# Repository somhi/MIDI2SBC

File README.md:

# MIDI I2S SBC Pmod Edge Interface

STATUS (26/12/22): Finished gerber files for v1.10. See changelog for updates from v0.7 to v1.1

STATUS (24/03/22): Finished most of testing satisfactorily. 

STATUS (24/03/22): received pcbs (16/03/22) and started testing.  

STATUS (01/03/22): sent v0.70 to manufacturing at JLCPCB

### Intro

This board was born as an addon for [NeptUNO](https://github.com/neptuno-fpga/Main_nepUNO/wiki) FPGA platform (although it can be linked to other FPGAs) for interfacing with a MIDI synthesizer (mt32-pi), DAC I2S, single board computers (or microcontrollers) and pmod peripherals.

This is my first PCB design attempt. 

Project has been developed with KiCAD 6.0.

This design is based on the Eagle design of the RTC+I2S+PIzero Addon by [Antonio Villena](https://www.antoniovillena.es/store/). I have to thank Antonio for his help.

### Flow diagram

### **Schematic**

[addon-edge-rpi-i2s-pmod.pdf](addon-edge-rpi-i2s-pmod.pdf)

### **Features**

* MIDI synthesizer: [mt32-pi](https://github.com/dwhinham/mt32-pi) 
  
  * Play MIDI sounds from FPGA core through an I2S DAC
  * It is possible to send mt32-pi I2S audio back to FPGA for mixing with other core audio and play it back through the I2S DAC
  * PCB includes footprints for an I2C OLED display, a rotative encoder and 2 buttons
  * Control mt32-pi through i2c pins (e.g. from MiSTer's OSD)
  
* DAC I2S: 
  
  * Play I2S audio sent from your FPGA (connected to Edge or Pmod 4)
  * Play I2S audio from Raspberry mt32-pi
  * PCB includes footprints for UDA 1334A and PCM5102A
  
* SBC / Micro-controller interface (Multicore)
  * Interface to FPGAs through Edge or Pmod 4 connectors
  * Interface signals: SPI (6 signals) and UART (Rx/Tx) 
  * PCB includes footprint for Raspberry Pi model B 40 pin connector. Other SBCs or microcontrollers can be interfaced through adapters (e.g. MAix BiT and STM32 adapters are available in [Atlas FPGA project](https://github.com/atlasfpga))
  * A SBC or uC could be used as a multicore device for the FPGA
  
* UART header connected to FPGA (Rx, Tx) (and Raspberry Pi also)

**Additional features for the Edge connector ** 

* Compatible platforms: NeptUNO, ZXDOS+ and GomaDOS+ from [Antonio Villena](https://www.antoniovillena.es/store/). 
  * NeptUNO base board is compatible with most of QMTech FPGAs
* PMODs 1 & 2 for double Pmod peripherals (like Hyperram, VGA, HDMI, ....)
  * Pmod 1 is connected to I2C lines of NeptUNO base board
  * Includes a 5V power supply header between Pmods  for broader compatibility
* PMODs 3 & 4  
  * Can be used as host or peripheral pmods (jumper JP5 enables output power). 
  * Includes a 5V power supply pin between Pmods  for broader compatibility
  * Notes:
    * Double Pmod for peripherals is only possible if not using mt32-pi or multicore options
    * Pmod 3 cannot be used with NeptUNO board cores usign SRAM

### 3D model

### **Usage notes**

* It is recommended to power supply first the FPGA and thereafter the MISI2SBC addon
  
* DAC I2S 
  
  * Only one DAC (either UDA 1334A or PCM5102A) is intended to be used at the same time, although should be possible to run them simultaneously.
  * DAC input voltage can be selected by jumpers from Edge, Raspberry Pi or other FPGA
  * PCM5102A connector is compatible with a 6 pin Pmod if JP11 jumper is removed.
  
* SPI communication between Raspberry Pi and FPGA
  * SPI 0 or SPI 1 is available (selection by jumpers JP4x) 
  * External FPGAs are to be connected to Pmod4 (SPI + UART)

* mt32-pi synthesizer
  * Power supply: JP11 set to RPI and short JP12 with a jumper
  * DAC source from FPGA: SPI 1 should be selected when using mt32-pi (jumpers JP4x)
  * DAC source from RPi: No jumper or SPI 0 should be selected when using mt32-pi (jumpers JP4x)
  * External FPGAs are to be connected to Pmod I2S (PCM5102A) and MIDI In (UART) or Pmod4 (SPI + UART) for mixing.
  * MiSTer OSD i2c control: short jumpers JP31, JP32 and remove jumpers from JP41, JP45.

### **Jumpers / Switches selection**

The board has several jumpers for a broader usage with multiple configurations. Instead of right angle pin headers with jumpers is also possible to use 3 pin mini switches.

**Jumper types**

* 2 pin jumper is either shorted (jumper on) or disconnected (without jumper)

* 3 pin jumper is either on one side or the other always connecting the central pin

**Jumper selection**

* DAC I2S Power supply input source  

  * JP11:  RPI / EDGE   (3 pin jumper)
    * RPI (5V from Raspberry Pi)
    * EDGE (5V from Edge connector (NeptUNO FPGA))
  * JP12  (2 pin jumper)

    * Jumper shorting JP11 and VIN (5V from selection of JP11 jumper is applied to VIN)
    * Without jumper (DAC power input comes from any VIN pin (J4, J5 or J12 Vin itself))

* DAC I2S Audio Source (3 pin jumper)
  * DAC I2S connected to FPGA: I2S sound from MIDI synthesizer mt32-pi (MIDI_CLKBD, MIDI_WSBD, MIDI_DABD signals) is routed to the FPGA (where could be mixed with other core sounds) and the FPGA sends the I2S signals back to the DAC I2S (BCLK, WSEL, DIN signals).
    * JP21, JP22, JP23 jumper connected to the FPGA mark side
  * DAC I2S connected directly to the MIDI synthesizer (mt32-pi)
    * JP21, JP22, JP23   jumper connected to the RPI mark side

* SPI / I2C selection  (2 pin jumpers)

  * SPI selection: JP31 and JP32 open.
  * I2C selection: JP31 and JP32 closed (central pins of MOSI JP41 and CE1 JP45 are wired to the I2C bus connected to the mt32-pi (RPi). Jumpers JP41 and JP45 should be removed to avoid interferences).

* SPI selection: SPI0 or SPI1 (3 pin jumper)

  * SPI0: JP41, JP42, JP43, JP44, JP45  jumper connected to the SPI0 mark side
  * SPI1: JP41, JP42, JP43, JP44, JP45  jumper connected to the SPI1 mark side

* Power supply selection for pins 1 and 2 of the I2C OLED display

  * You might find in the marked I2C displays that need 3V3 on pin 1 and GND on pin 2 whereas others those pins are exchanged

  * JPS1 is a 3 pad solder jumper

    * Solder central pad to either 3V3 or GND for selecting function of PS1 display pin 1

  * JPS2 is a 3 pad solder jumper

    * Solder central pad to either 3V3 or GND for selecting function of PS2 display pin 2

* Power supply for PMOD3 & PMOD4 ( JP5 2 pin jumper )

  * Use as Peripheral pmods: JP5 opened  (No voltage is supplied into VH pins)
  * Use as Host pmods: JP5 closed (3V3 voltage from board is wired into VH pins)

### Notes regarding NeptUNO base board

* Following shared pins of Pmod 1 will only work with slow signals because they are connected to the I2C circuit of the VGA monitor. 

```
PMOD1_D2   I2C SCL    RTC,   VGA  
PMOD1_D3   I2C SDA    RTC,   VGA  
```

A simple way to solve this is to remove pins 12 and 15 with a plier from the VGA connector of the extension cable to the monitor as shown in the following picture:

* In order to use PMOD1_D5 pin it is required to configure in Quartus as following (Device and Pin Options : Dual-Purpose Pins: nCEO : Use as regular I/O)

* B24 Edge pin is connected in NeptUNO board internally to the Joy Select signal by means of a solder pad which by default is not soldered. To get this signal in the addon it is required to solder the two pads of the left as seen in the following picture.

  Please notice that it is better not to use the Joy Select pin if you intend the use also pin 7 on DB9 connectors of NeptUNO board for the joy select function of Sega megadrive joysticks.

### Changelog

v0.42  last version with 25 pins

v0.50  added 10 more pins connected at Edge connector to FPGA. Those pins are shared with other peripherals (2 pins bus I2C shared with RTC and VGA connector, 8 pins shared with SRAM memory)

v0.60  routed and gerber done

**v0.70** minor changes. Prototype version sent to manufacturing

v0.71 corrected minor misalignment between Pmod 1 and Pmod 2

v0.72 silkscreen updated (midi and mt32pi settings)

v1.00 silkscreen and documentation improved. Pmod3 and Pmod4 silkscreen labels exchanged. Rounded corners of outline. Pmod3/4 moved 0.4 mm outside.

v1.01 silkscreen for pmod i2s (PCM5102A connector). Improved usage notes in readme.

v1.02 minor silkscreen changes, usage notes.

v1.05 minor silkscreen changes

v1.10 routed i2c pins to PMOD 4 to communicate Raspberry Pi and FPGA (e.g. MiSTer can control mt32-pi from OSD)

### **Todo / Improvements**

* Mechanical stability of i2S DACs and display could be improved. -> Solution: bending a little bit the pins from the display and the DAC I2S so they fix better to the board sockets and don't move.

* Add in the same PCB a breokout board for converting PMO4 to USB3 for MiSTer connection

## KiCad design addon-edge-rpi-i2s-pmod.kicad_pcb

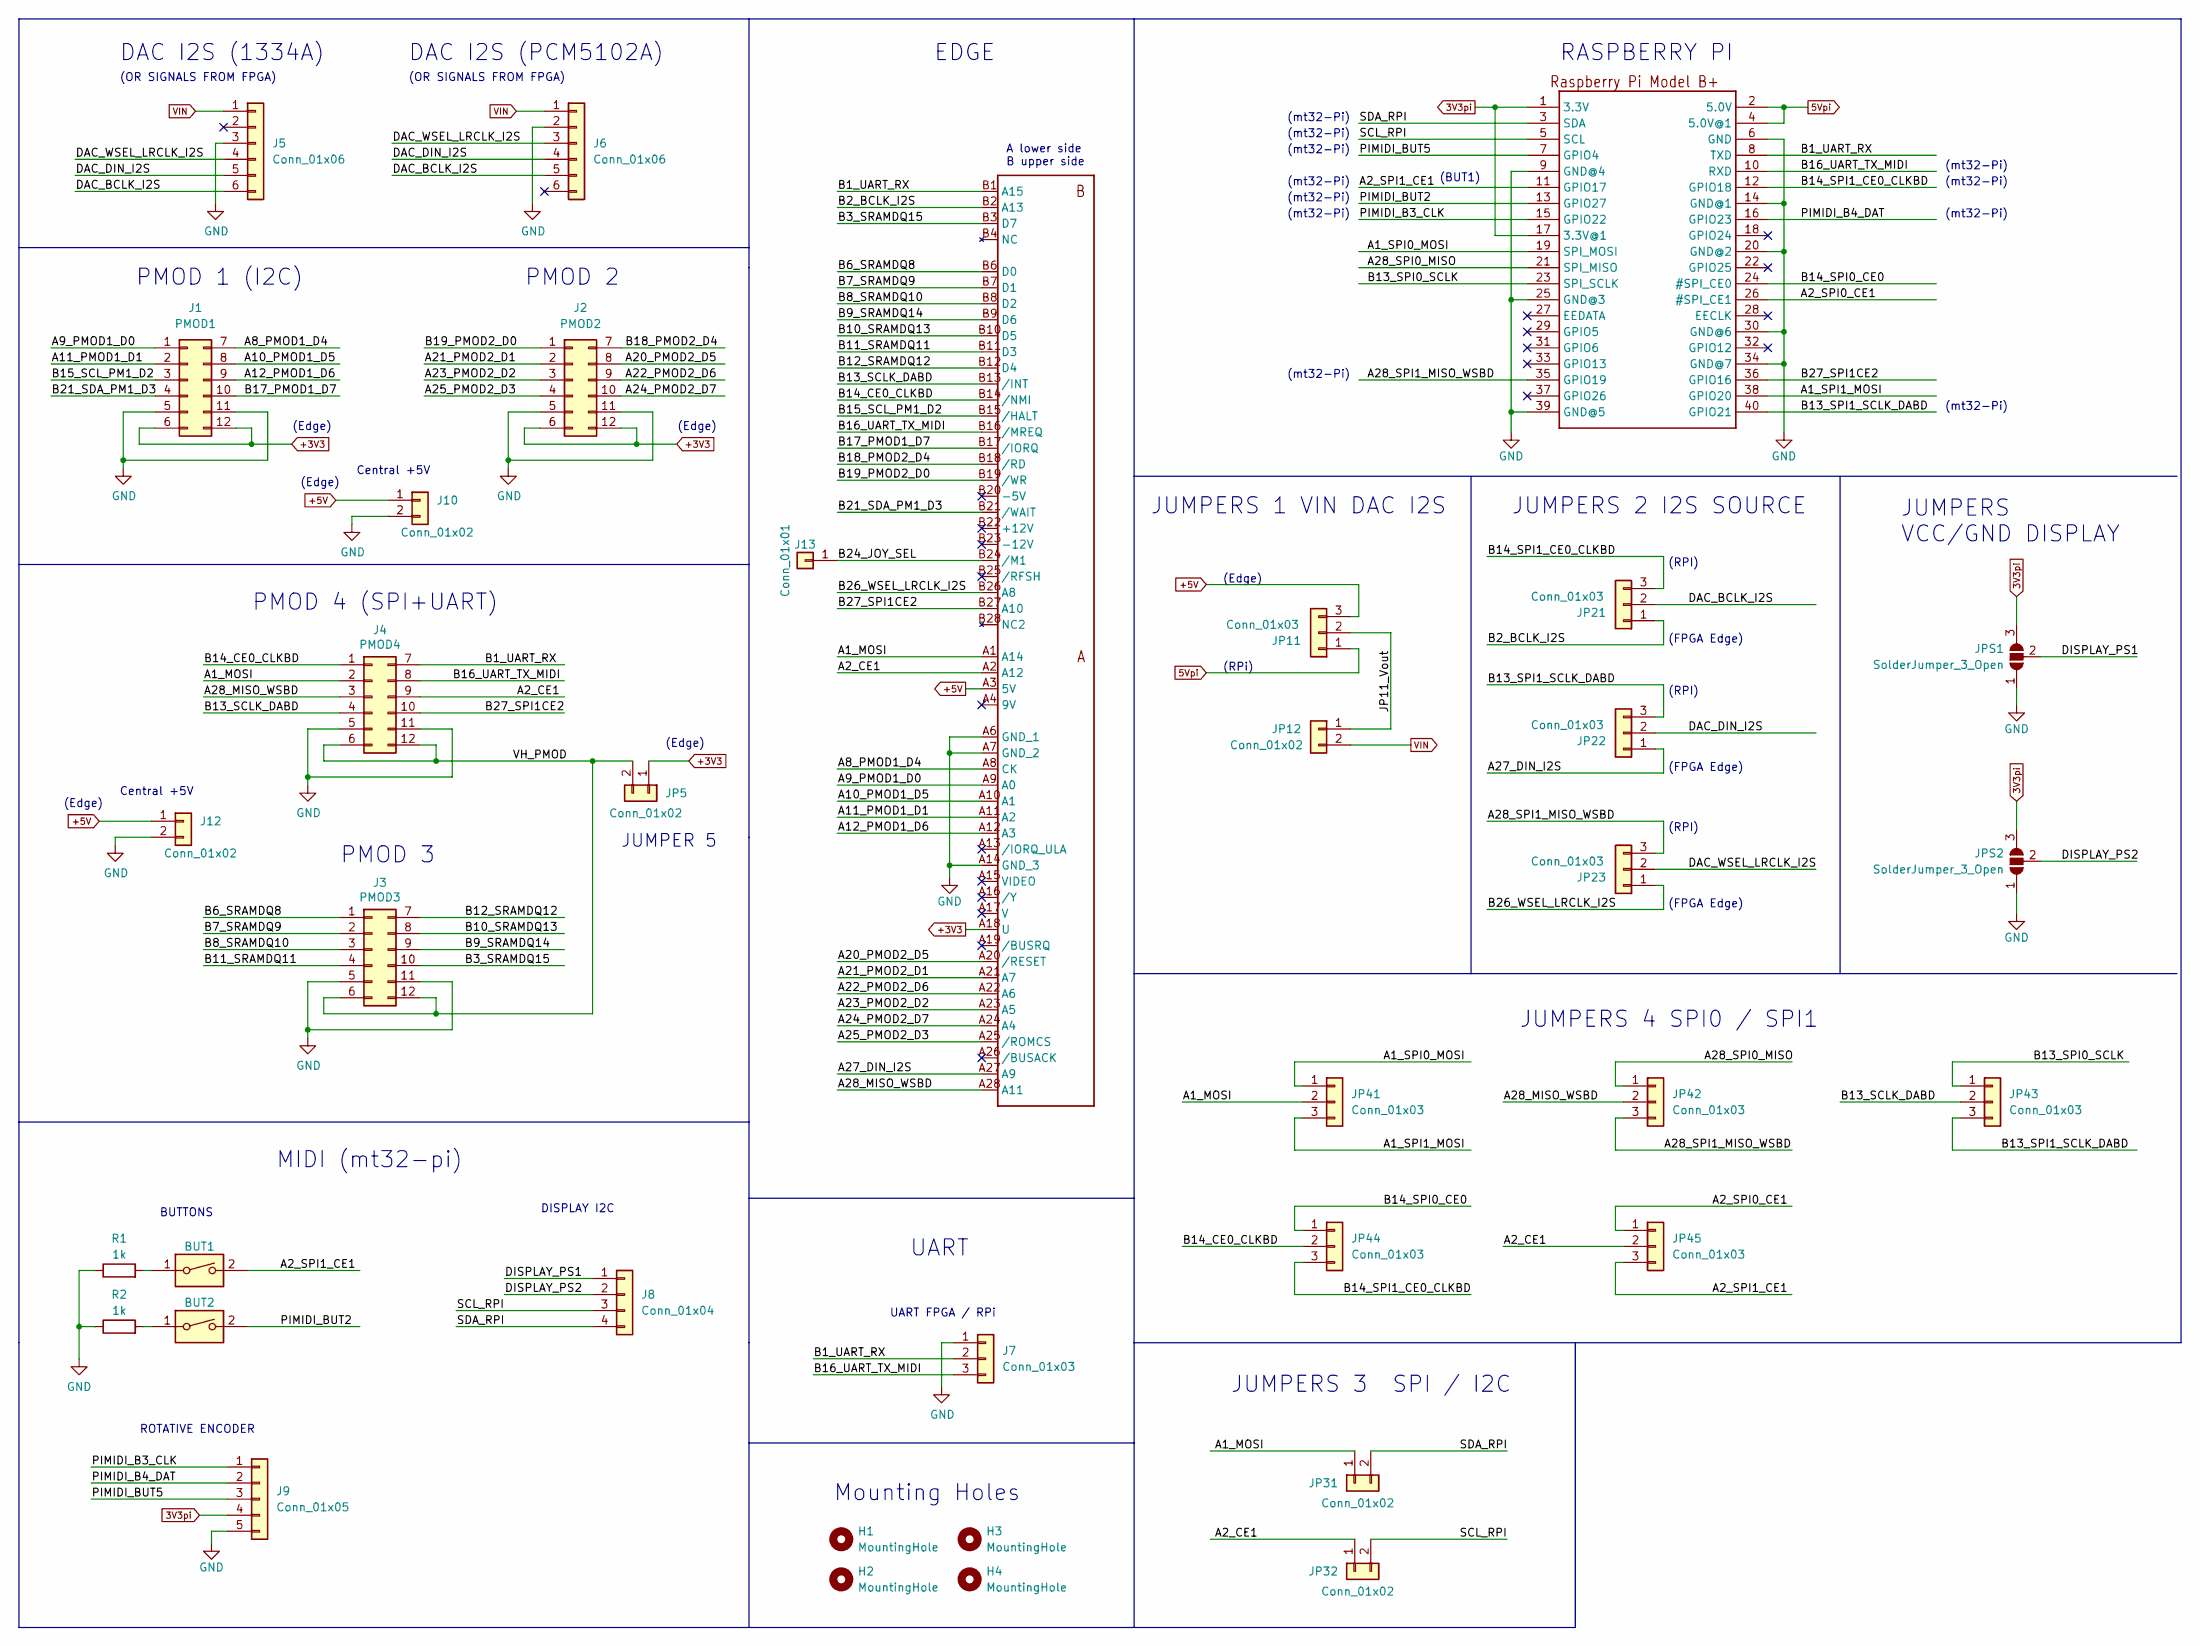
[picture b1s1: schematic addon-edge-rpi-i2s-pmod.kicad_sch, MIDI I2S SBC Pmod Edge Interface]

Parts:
BUT1, BUT2: SW_DIP_x01; SW_PUSH_6mm_H5mm
EDGE1: ZXSP_ED2X28_SPE_SOL_EDGE; 2X28_SPE2
H1, H2, H3, H4: MountingHole; MountingHole_3.2mm_M3
J1: PMOD1; Pmod_2x06_P2.54mm_Vertical_2
J2: PMOD2; Pmod_2x06_P2.54mm_Vertical_2
J3: PMOD3; PMOD_Female_Horizontal_2
J4: PMOD4; PMOD_Female_Horizontal_2
J5: Conn_01x06; UDA1334
J6: Conn_01x06; PCM5102
J7: Conn_01x03; PinHeader_1x03_P2.54mm_Vertical
J8: Conn_01x04; I2C_DISPLAY_MULTI2
J9: Conn_01x05; PinSocket_1x05_P2.54mm_Vertical
J10: Conn_01x02; PinSocket_1x02_P2.54mm_Vertical
J12: Conn_01x02; PinSocket_2x01_P2.54mm_Horizontal
J13: Conn_01x01; PinHeader_1x01_P2.54mm_Vertical
JP5, JP31, JP32: Conn_01x02; PinHeader_1x02_P2.54mm_Vertical
JP11, JP21, JP22, JP23, JP41, JP42, JP43, JP44, JP45: Conn_01x03; PinHeader_1x03_P2.54mm_Horizontal
JP12: Conn_01x02; PinHeader_1x02_P2.54mm_Horizontal
JPS1, JPS2: SolderJumper_3_Open; SolderJumper-3_P1.3mm_Open_RoundedPad1.0x1.5mm_NumberLabels
R1, R2: 1k; R_1206_3216Metric_Pad1.30x1.75mm_HandSolder
RPI1: RASPBERRYPI_BPLUS_BONNETNODIM; PinSocket_2x20_P2.54mm_Vertical

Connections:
3V3pi: J9.4, JPS1.3 (B), JPS2.3 (B), RPI1.1 (3.3V), RPI1.17 (3.3V@1)
5Vpi: JP11.1, RPI1.2 (5.0V), RPI1.4 (5.0V@1)
+3V3: EDGE1.A18 (U), J1.6, J1.12, J2.6, J2.12, JP5.1
+5V: EDGE1.A3 (5V), J10.1, J12.1, JP11.3
/A1_MOSI: EDGE1.A1 (A14), J4.2, JP31.1, JP41.2
/A1_SPI0_MOSI: JP41.1, RPI1.19 (SPI_MOSI)
/A1_SPI1_MOSI: JP41.3, RPI1.38 (GPIO20)
/A2_CE1: EDGE1.A2 (A12), J4.9, JP32.1, JP45.2
/A2_SPI0_CE1: JP45.1, RPI1.26 (#SPI_CE1)
/A2_SPI1_CE1: BUT1.2, JP45.3, RPI1.11 (GPIO17)
/A8_PMOD1_D4: EDGE1.A8 (CK), J1.7
/A9_PMOD1_D0: EDGE1.A9 (A0), J1.1
/A10_PMOD1_D5: EDGE1.A10 (A1), J1.8
/A11_PMOD1_D1: EDGE1.A11 (A2), J1.2
/A12_PMOD1_D6: EDGE1.A12 (A3), J1.9
/A20_PMOD2_D5: EDGE1.A20 (/RESET), J2.8
/A21_PMOD2_D1: EDGE1.A21 (A7), J2.2
/A22_PMOD2_D6: EDGE1.A22 (A6), J2.9
/A23_PMOD2_D2: EDGE1.A23 (A5), J2.3
/A24_PMOD2_D7: EDGE1.A24 (A4), J2.10
/A25_PMOD2_D3: EDGE1.A25 (/ROMCS), J2.4
/A27_DIN_I2S: EDGE1.A27 (A9), JP22.1
/A28_MISO_WSBD: EDGE1.A28 (A11), J4.3, JP42.2
/A28_SPI0_MISO: JP42.1, RPI1.21 (SPI_MISO)
/A28_SPI1_MISO_WSBD: JP23.3, JP42.3, RPI1.35 (GPIO19)
/B1_UART_RX: EDGE1.B1 (A15), J4.7, J7.2, RPI1.8 (TXD)
/B2_BCLK_I2S: EDGE1.B2 (A13), JP21.1
/B3_SRAMDQ15: EDGE1.B3 (D7), J3.10
/B6_SRAMDQ8: EDGE1.B6 (D0), J3.1
/B7_SRAMDQ9: EDGE1.B7 (D1), J3.2
/B8_SRAMDQ10: EDGE1.B8 (D2), J3.3
/B9_SRAMDQ14: EDGE1.B9 (D6), J3.9
/B10_SRAMDQ13: EDGE1.B10 (D5), J3.8
/B11_SRAMDQ11: EDGE1.B11 (D3), J3.4
/B12_SRAMDQ12: EDGE1.B12 (D4), J3.7
/B13_SCLK_DABD: EDGE1.B13 (/INT), J4.4, JP43.2
/B13_SPI0_SCLK: JP43.1, RPI1.23 (SPI_SCLK)
/B13_SPI1_SCLK_DABD: JP22.3, JP43.3, RPI1.40 (GPIO21)
/B14_CE0_CLKBD: EDGE1.B14 (/NMI), J4.1, JP44.2
/B14_SPI0_CE0: JP44.1, RPI1.24 (#SPI_CE0)
/B14_SPI1_CE0_CLKBD: JP21.3, JP44.3, RPI1.12 (GPIO18)
/B15_SCL_PM1_D2: EDGE1.B15 (/HALT), J1.3
/B16_UART_TX_MIDI: EDGE1.B16 (/MREQ), J4.8, J7.3, RPI1.10 (RXD)
/B17_PMOD1_D7: EDGE1.B17 (/IORQ), J1.10
/B18_PMOD2_D4: EDGE1.B18 (/RD), J2.7
/B19_PMOD2_D0: EDGE1.B19 (/WR), J2.1
/B21_SDA_PM1_D3: EDGE1.B21 (/WAIT), J1.4
/B24_JOY_SEL: EDGE1.B24 (/M1), J13.1
/B26_WSEL_LRCLK_I2S: EDGE1.B26 (A8), JP23.1
/B27_SPI1CE2: EDGE1.B27 (A10), J4.10, RPI1.36 (GPIO16)
/DAC_BCLK_I2S: J5.6, J6.5, JP21.2
/DAC_DIN_I2S: J5.5, J6.4, JP22.2
/DAC_WSEL_LRCLK_I2S: J5.4, J6.3, JP23.2
/DISPLAY_PS1: J8.1, JPS1.2 (C)
/DISPLAY_PS2: J8.2, JPS2.2 (C)
/JP11_Vout: JP11.2, JP12.1
/PIMIDI_B3_CLK: J9.1, RPI1.15 (GPIO22)
/PIMIDI_B4_DAT: J9.2, RPI1.16 (GPIO23)
/PIMIDI_BUT2: BUT2.2, RPI1.13 (GPIO27)
/PIMIDI_BUT5: J9.3, RPI1.7 (GPIO4)
/SCL_RPI: J8.3, JP32.2, RPI1.5 (SCL)
/SDA_RPI: J8.4, JP31.2, RPI1.3 (SDA)
/VH_PMOD: J3.6, J3.12, J4.6, J4.12, JP5.2
GND: EDGE1.A6 (GND_1), EDGE1.A7 (GND_2), EDGE1.A14 (GND_3), J1.5, J1.11, J2.5, J2.11, J3.5, J3.11, J4.5, J4.11, J5.3, J6.2, J7.1, J9.5, J10.2, J12.2, JPS1.1 (A), JPS2.1 (A), R1.1, R2.1, RPI1.6 (GND), RPI1.9 (GND@4), RPI1.14 (GND@1), RPI1.20 (GND@2), RPI1.25 (GND@3), RPI1.30 (GND@6), RPI1.34 (GND@7), RPI1.39 (GND@5)
unnamed: BUT1.1, R1.2
unnamed: BUT2.1, R2.2
VIN: J5.1, J6.1, JP12.2

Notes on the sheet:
JUMPERS 1 VIN DAC I2S
(mt32-Pi)
JUMPERS VCC/GND DISPLAY
PMOD 3
Central +5V
JUMPERS 4 SPI0 / SPI1
(RPI)
JUMPERS 2 I2S SOURCE
(OR SIGNALS FROM FPGA)
PMOD 4 (SPI+UART)
PMOD 1 (I2C)
Mounting Holes
UART FPGA / RPi
DISPLAY I2C
EDGE
(FPGA Edge)
(Edge)
(BUT1)
RASPBERRY PI
JUMPERS 3 SPI / I2C
UART
MIDI (mt32-pi)
JUMPER 5
ROTATIVE ENCODER
BUTTONS
(RPi)
PMOD 2
DAC I2S (1334A)
A lower side B upper side
DAC I2S (PCM5102A)

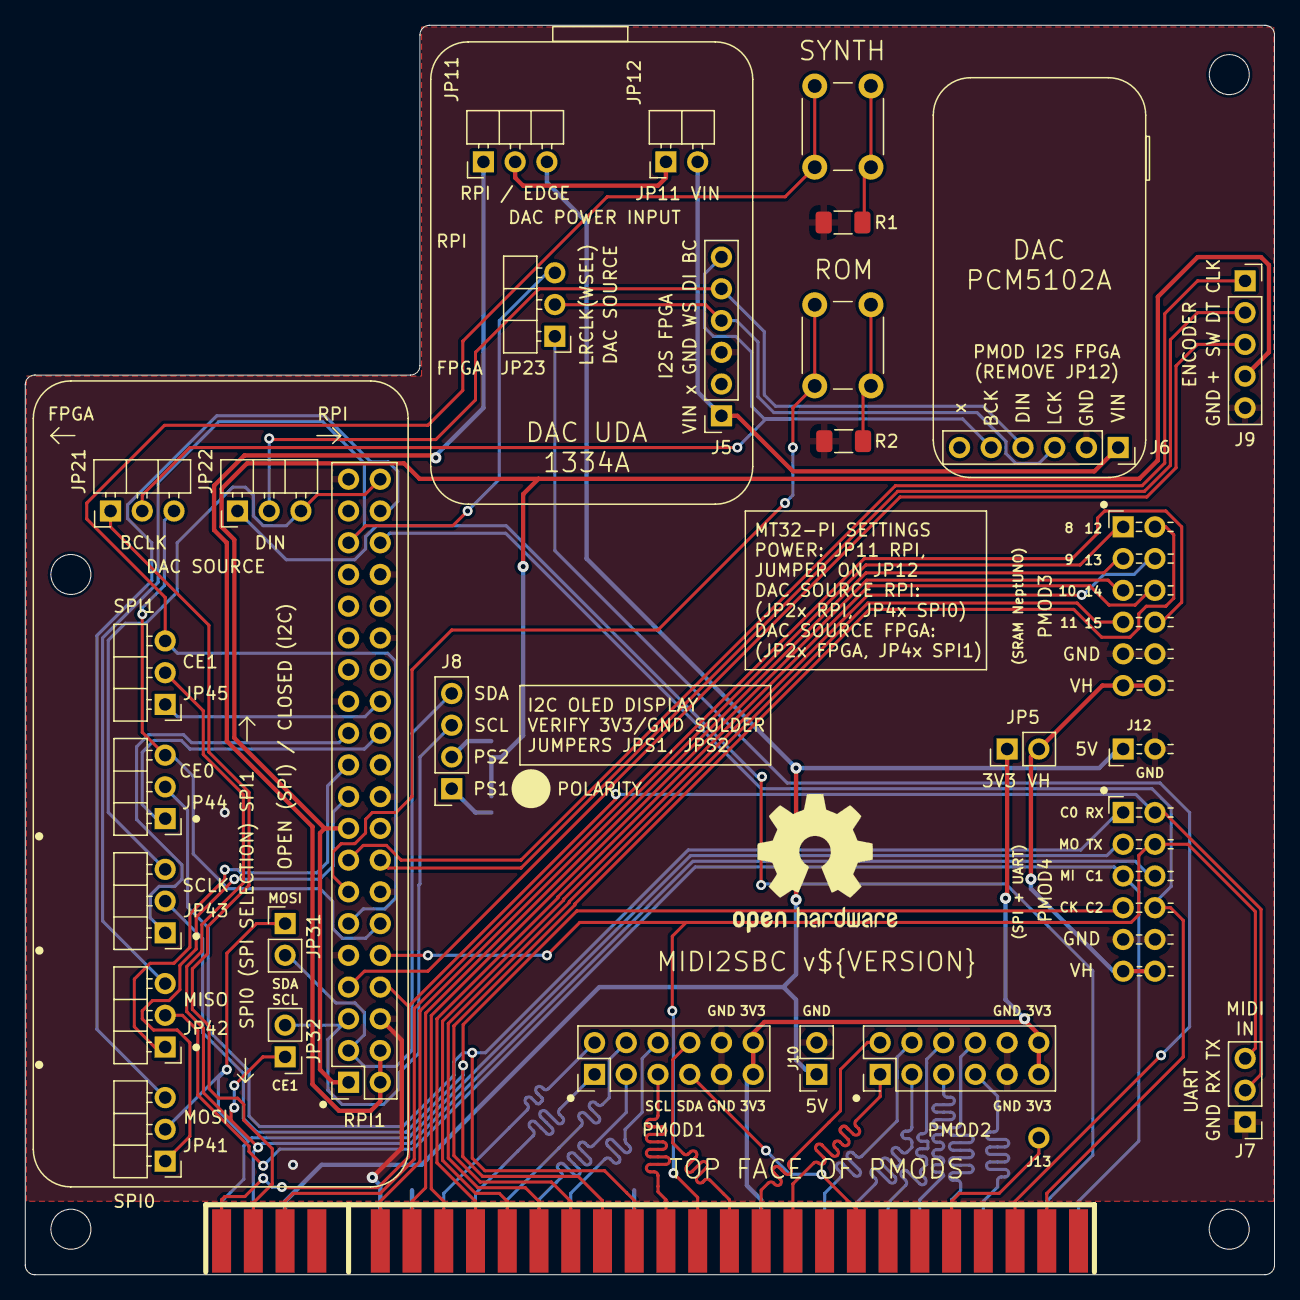
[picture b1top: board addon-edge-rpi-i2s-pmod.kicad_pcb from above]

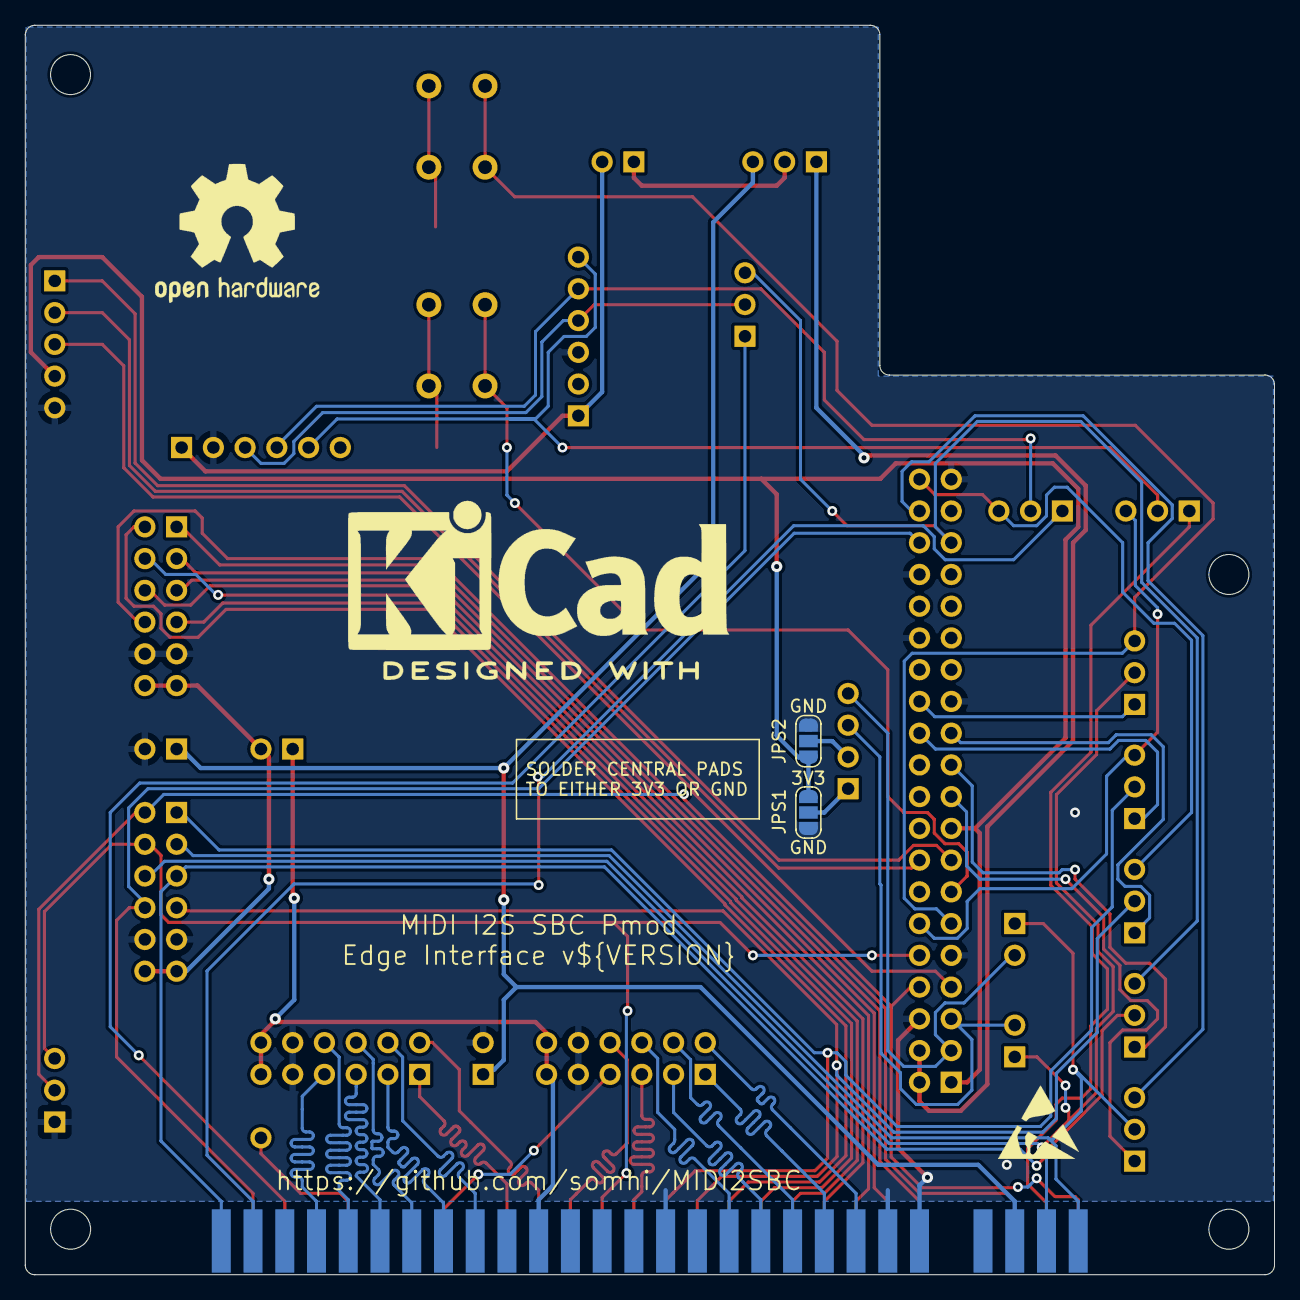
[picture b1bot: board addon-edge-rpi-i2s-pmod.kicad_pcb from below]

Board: 2 copper layers, 100.0 x 100.0 mm, 41 parts (5 on the bottom side), 67 nets.

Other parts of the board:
LO1: KiCad-Logo2_12mm_SilkScreen
LO2, LO3: OSHW-Logo2_14.6x12mm_SilkScreen
LO4: ESD-Logo_6.6x6mm_SilkScreen

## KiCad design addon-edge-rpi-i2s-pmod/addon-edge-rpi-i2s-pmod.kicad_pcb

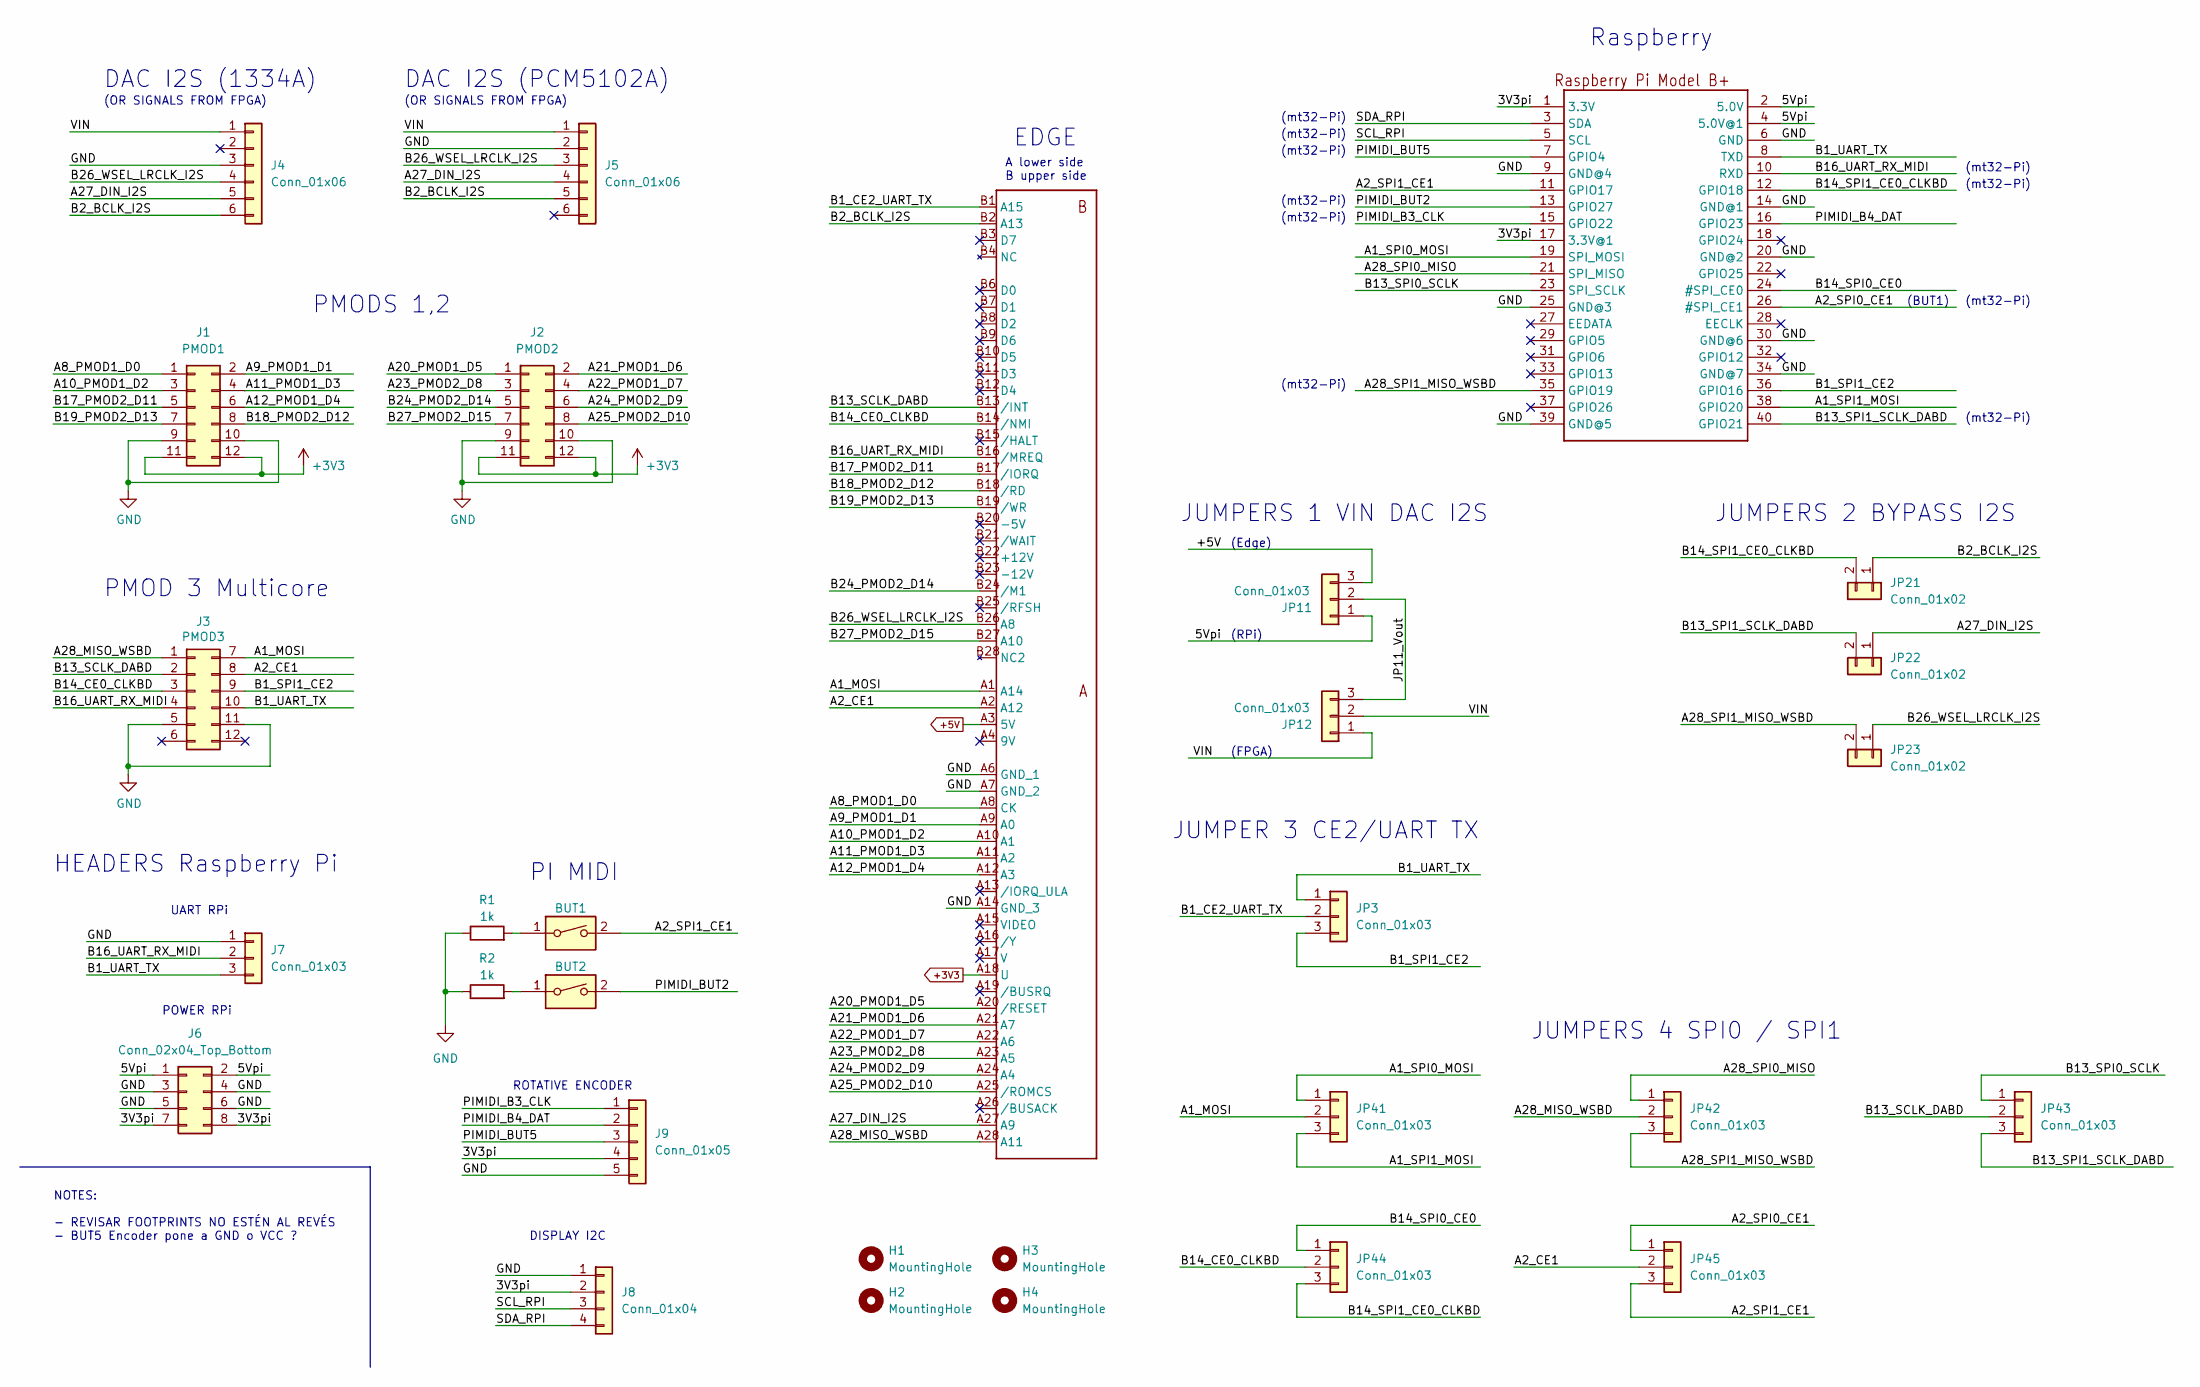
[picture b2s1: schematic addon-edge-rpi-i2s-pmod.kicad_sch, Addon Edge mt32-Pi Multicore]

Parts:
BUT1, BUT2: SW_DIP_x01; SW_PUSH_6mm_H5mm
EDGE1: ZXSP_ED2X28_SPE_SOL_EDGE; 2X28_SPE2
H1, H2, H3, H4: MountingHole; MountingHole_3.2mm_M3
J1: PMOD1; PinSocket_2x06_P2.54mm_Vertical
J2: PMOD2; PinSocket_2x06_P2.54mm_Vertical
J3: PMOD3; PMOD_Female_Horizontal_2
J4: Conn_01x06; UDA1334
J5: Conn_01x06; PCM5102
J6: Conn_02x04_Top_Bottom; PinSocket_2x04_P2.54mm_Vertical
J7: Conn_01x03; PinHeader_1x03_P2.54mm_Vertical
J8: Conn_01x04; OLED_091_DISPLAY
J9: Conn_01x05; PinSocket_1x05_P2.54mm_Vertical
JP3: Conn_01x03; PinHeader_1x03_P2.54mm_Vertical
JP11, JP12, JP41, JP42, JP43, JP44, JP45: Conn_01x03; PinHeader_1x03_P2.54mm_Horizontal
JP21, JP22, JP23: Conn_01x02; PinHeader_1x02_P2.54mm_Horizontal
R1, R2: 1k; R_1206_3216Metric_Pad1.30x1.75mm_HandSolder
RPI1: RASPBERRYPI_BPLUS_BONNETNODIM; PinSocket_2x20_P2.54mm_Vertical

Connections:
+3V3: EDGE1.A18 (U), J1.11, J1.12, J2.11, J2.12
+5V: EDGE1.A3 (5V), JP11.3
/3V3pi: J6.7, J6.8, J8.2, J9.4, RPI1.1 (3.3V), RPI1.17 (3.3V@1)
/5Vpi: J6.1, J6.2, JP11.1, RPI1.2 (5.0V), RPI1.4 (5.0V@1)
/A1_MOSI: EDGE1.A1 (A14), J3.7, JP41.2
/A1_SPI0_MOSI: JP41.1, RPI1.19 (SPI_MOSI)
/A1_SPI1_MOSI: JP41.3, RPI1.38 (GPIO20)
/A2_CE1: EDGE1.A2 (A12), J3.8, JP45.2
/A2_SPI0_CE1: JP45.1, RPI1.26 (#SPI_CE1)
/A2_SPI1_CE1: BUT1.2, JP45.3, RPI1.11 (GPIO17)
/A8_PMOD1_D0: EDGE1.A8 (CK), J1.1
/A9_PMOD1_D1: EDGE1.A9 (A0), J1.2
/A10_PMOD1_D2: EDGE1.A10 (A1), J1.3
/A11_PMOD1_D3: EDGE1.A11 (A2), J1.4
/A12_PMOD1_D4: EDGE1.A12 (A3), J1.6
/A20_PMOD1_D5: EDGE1.A20 (/RESET), J2.1
/A21_PMOD1_D6: EDGE1.A21 (A7), J2.2
/A22_PMOD1_D7: EDGE1.A22 (A6), J2.4
/A23_PMOD2_D8: EDGE1.A23 (A5), J2.3
/A24_PMOD2_D9: EDGE1.A24 (A4), J2.6
/A25_PMOD2_D10: EDGE1.A25 (/ROMCS), J2.8
/A27_DIN_I2S: EDGE1.A27 (A9), J4.5, J5.4, JP22.1
/A28_MISO_WSBD: EDGE1.A28 (A11), J3.1, JP42.2
/A28_SPI0_MISO: JP42.1, RPI1.21 (SPI_MISO)
/A28_SPI1_MISO_WSBD: JP23.2, JP42.3, RPI1.35 (GPIO19)
/B1_CE2_UART_TX: EDGE1.B1 (A15), JP3.2
/B1_SPI1_CE2: J3.9, JP3.3, RPI1.36 (GPIO16)
/B1_UART_TX: J3.10, J7.3, JP3.1, RPI1.8 (TXD)
/B2_BCLK_I2S: EDGE1.B2 (A13), J4.6, J5.5, JP21.1
/B13_SCLK_DABD: EDGE1.B13 (/INT), J3.2, JP43.2
/B13_SPI0_SCLK: JP43.1, RPI1.23 (SPI_SCLK)
/B13_SPI1_SCLK_DABD: JP22.2, JP43.3, RPI1.40 (GPIO21)
/B14_CE0_CLKBD: EDGE1.B14 (/NMI), J3.3, JP44.2
/B14_SPI0_CE0: JP44.1, RPI1.24 (#SPI_CE0)
/B14_SPI1_CE0_CLKBD: JP21.2, JP44.3, RPI1.12 (GPIO18)
/B16_UART_RX_MIDI: EDGE1.B16 (/MREQ), J3.4, J7.2, RPI1.10 (RXD)
/B17_PMOD2_D11: EDGE1.B17 (/IORQ), J1.5
/B18_PMOD2_D12: EDGE1.B18 (/RD), J1.8
/B19_PMOD2_D13: EDGE1.B19 (/WR), J1.7
/B24_PMOD2_D14: EDGE1.B24 (/M1), J2.5
/B26_WSEL_LRCLK_I2S: EDGE1.B26 (A8), J4.4, J5.3, JP23.1
/B27_PMOD2_D15: EDGE1.B27 (A10), J2.7
/JP11_Vout: JP11.2, JP12.3
/PIMIDI_B3_CLK: J9.1, RPI1.15 (GPIO22)
/PIMIDI_B4_DAT: J9.2, RPI1.16 (GPIO23)
/PIMIDI_BUT2: BUT2.2, RPI1.13 (GPIO27)
/PIMIDI_BUT5: J9.3, RPI1.7 (GPIO4)
/SCL_RPI: J8.3, RPI1.5 (SCL)
/SDA_RPI: J8.4, RPI1.3 (SDA)
/VIN: J4.1, J5.1, JP12.1, JP12.2
GND: EDGE1.A6 (GND_1), EDGE1.A7 (GND_2), EDGE1.A14 (GND_3), J1.9, J1.10, J2.9, J2.10, J3.5, J3.11, J4.3, J5.2, J6.3, J6.4, J6.5, J6.6, J7.1, J8.1, J9.5, R1.1, R2.1, RPI1.6 (GND), RPI1.9 (GND@4), RPI1.14 (GND@1), RPI1.20 (GND@2), RPI1.25 (GND@3), RPI1.30 (GND@6), RPI1.34 (GND@7), RPI1.39 (GND@5)
unnamed: BUT1.1, R1.2
unnamed: BUT2.1, R2.2

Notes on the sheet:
JUMPERS 1 VIN DAC I2S
(mt32-Pi)
JUMPERS 4 SPI0 / SPI1
JUMPERS 2 BYPASS I2S
(OR SIGNALS FROM FPGA)
PMOD 3 Multicore
(FPGA)
PMODS 1,2
UART RPi
DISPLAY I2C
EDGE
Raspberry
(BUT1)
HEADERS Raspberry Pi
PI MIDI
ROTATIVE ENCODER
POWER RPi
NOTES: - REVISAR FOOTPRINTS NO ESTÉN AL REVÉS - BUT5 Encoder pone a GND o VCC ?
(Edge)
(RPi)
DAC I2S (1334A)
A lower side B upper side
DAC I2S (PCM5102A)
JUMPER 3 CE2/UART TX

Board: 2 copper layers, 32 parts (2 on the bottom side), 53 nets, no tracks yet.

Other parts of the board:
ESD1: ESD-Logo_6.6x6mm_SilkScreen
OH1: OSHW-Logo2_14.6x12mm_SilkScreen

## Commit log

2022-02-09 rev. 0.38
2022-02-10 update 10/02/22 initial autorouting
2022-02-12 rev 0.40
2022-02-13 rev. 0.41
2022-02-13 updated readme and added datasheets info folder
2022-02-14 0.42
2022-02-15 modified jumper spacing for allowing switches
2022-02-22 v0.50 major changes
2022-02-22 flow diagram updated
2022-02-23 v0.51 manual routing finished
2022-02-23 readme updated
2022-02-24 v0.52 changed tracks pmod 1 & 2
2022-02-25 generated gerber files
2022-02-25 v0.6 silkscreen and gerber updated
2022-02-26 updated readme status
2022-02-28 v0.7 sent to manufacturing
2022-03-13 v0.71 minor disalignment of pmods 1/2
2022-03-19 v0.72 silkscreen updated
2022-03-20 comments on schematic
2022-03-24 v1.00 minor changes after testing manufactured v0.7
2022-03-25 silkscreen mod from v0.7 to v1.0
2022-03-28 v1.01 pmod i2s
2022-04-09 v1.02 minor silkscreen updates
2022-11-22 v1.05 minor silkscreen changes
2022-11-22 changed repository name
2022-11-22 v1.10 added i2c jumpers to control mt32-pi from fpga
2022-12-26 v.1.10 generated gerber files for production
2023-01-31 updated .ods BOM with purchase links

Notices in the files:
addon-edge-rpi-i2s-pmod.kicad_pcb:
License: CC-BY.SA v4.0
